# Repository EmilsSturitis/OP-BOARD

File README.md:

# OP-BOARD
Operational amplifier dev board based on the OPA2333

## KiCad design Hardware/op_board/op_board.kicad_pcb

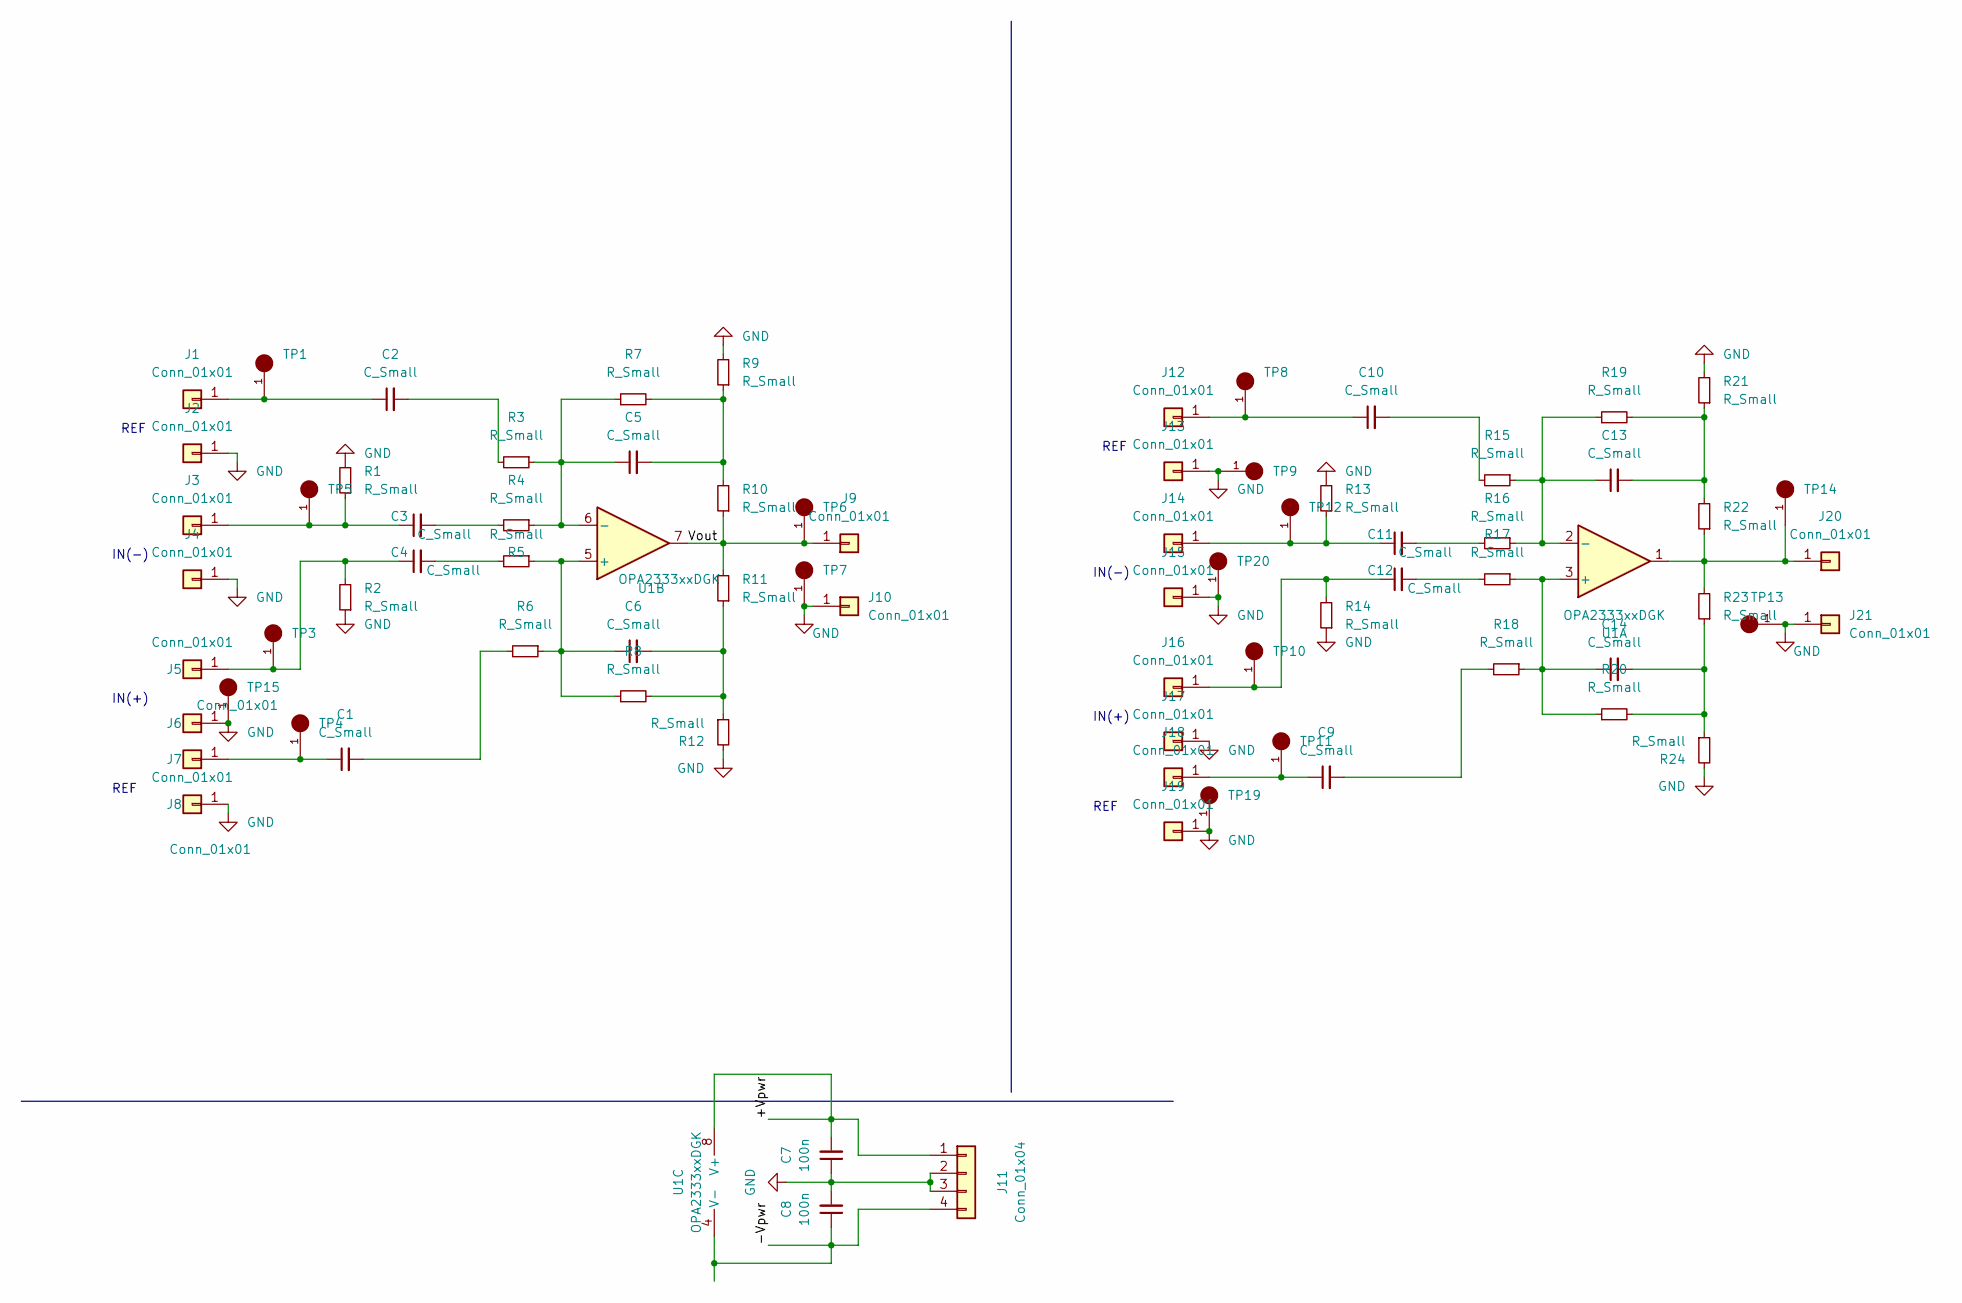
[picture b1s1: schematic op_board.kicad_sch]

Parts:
C1, C2, C3, C4, C5, C6, C9, C10, C11, C12, C13, C14: C_Small; C_0805_2012Metric_Pad1.18x1.45mm_HandSolder
C7, C8: 100n; C_0603_1608Metric
J1, J3, J5, J7, J9, J12, J14, J16, J18, J20: Conn_01x01; TestPoint_THTPad_2.0x2.0mm_Drill1.0mm
J2, J4, J6, J8, J10, J13, J15, J17, J19, J21: Conn_01x01; TestPoint_THTPad_D2.0mm_Drill1.0mm
J11: Conn_01x04; PinHeader_1x04_P2.54mm_Vertical
R1, R2, R3, R4, R5, R6, R7, R8, R9, R10, R11, R12, R13, R14, R15, R16, R17, R18, R19, R20, R21, R22, R23, R24: R_Small; R_0805_2012Metric_Pad1.20x1.40mm_HandSolder
TP1, TP3, TP4, TP5, TP6, TP7, TP8, TP9, TP10, TP11, TP12, TP13, TP14, TP15, TP19, TP20: RCWCTE; TP420X150; PARTREV 1/06/14
U1: OPA2333xxDGK; TSSOP-8_3x3mm_P0.65mm

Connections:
/+Vpwr: C7.2, J11.1, U1.8 (V+)
/-Vpwr: C8.1, J11.4, U1.4 (V-)
/Vout: J9.1, R10.1, R11.2, TP6.1, U1.7
GND: C7.1, C8.2, J2.1, J4.1, J6.1, J8.1, J10.1, J11.2, J11.3, J13.1, J15.1, J17.1, J19.1, J21.1, R1.2, R2.1, R9.2, R12.2, R13.2, R14.1, R21.2, R24.2, TP7.1, TP9.1, TP13.1, TP15.1, TP19.1, TP20.1
unnamed: C1.2, R6.2
unnamed: C2.2, R3.2
unnamed: C3.2, R4.2
unnamed: C4.2, R5.2
unnamed: C5.2, R7.2, R9.1, R10.2
unnamed: C6.2, R8.2, R11.1, R12.1
unnamed: C9.2, R18.2
unnamed: C10.2, R15.2
unnamed: C11.2, R16.2
unnamed: C12.2, R17.2
unnamed: C13.2, R19.2, R21.1, R22.2
unnamed: C14.2, R20.2, R23.1, R24.1
unnamed: C2.1, J1.1, TP1.1
unnamed: C3.1, J3.1, R1.1, TP5.1
unnamed: C4.1, J5.1, R2.2, TP3.1
unnamed: C1.1, J7.1, TP4.1
unnamed: C10.1, J12.1, TP8.1
unnamed: C11.1, J14.1, R13.1, TP12.1
unnamed: C12.1, J16.1, R14.2, TP10.1
unnamed: C9.1, J18.1, TP11.1
unnamed: J20.1, R22.1, R23.2, TP14.1, U1.1
unnamed: C14.1, R17.1, R18.1, R20.1, U1.3 (+)
unnamed: C13.1, R15.1, R16.1, R19.1, U1.2 (-)
unnamed: C6.1, R5.1, R6.1, R8.1, U1.5 (+)
unnamed: C5.1, R3.1, R4.1, R7.1, U1.6 (-)

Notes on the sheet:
IN(-)
IN(+)
REF

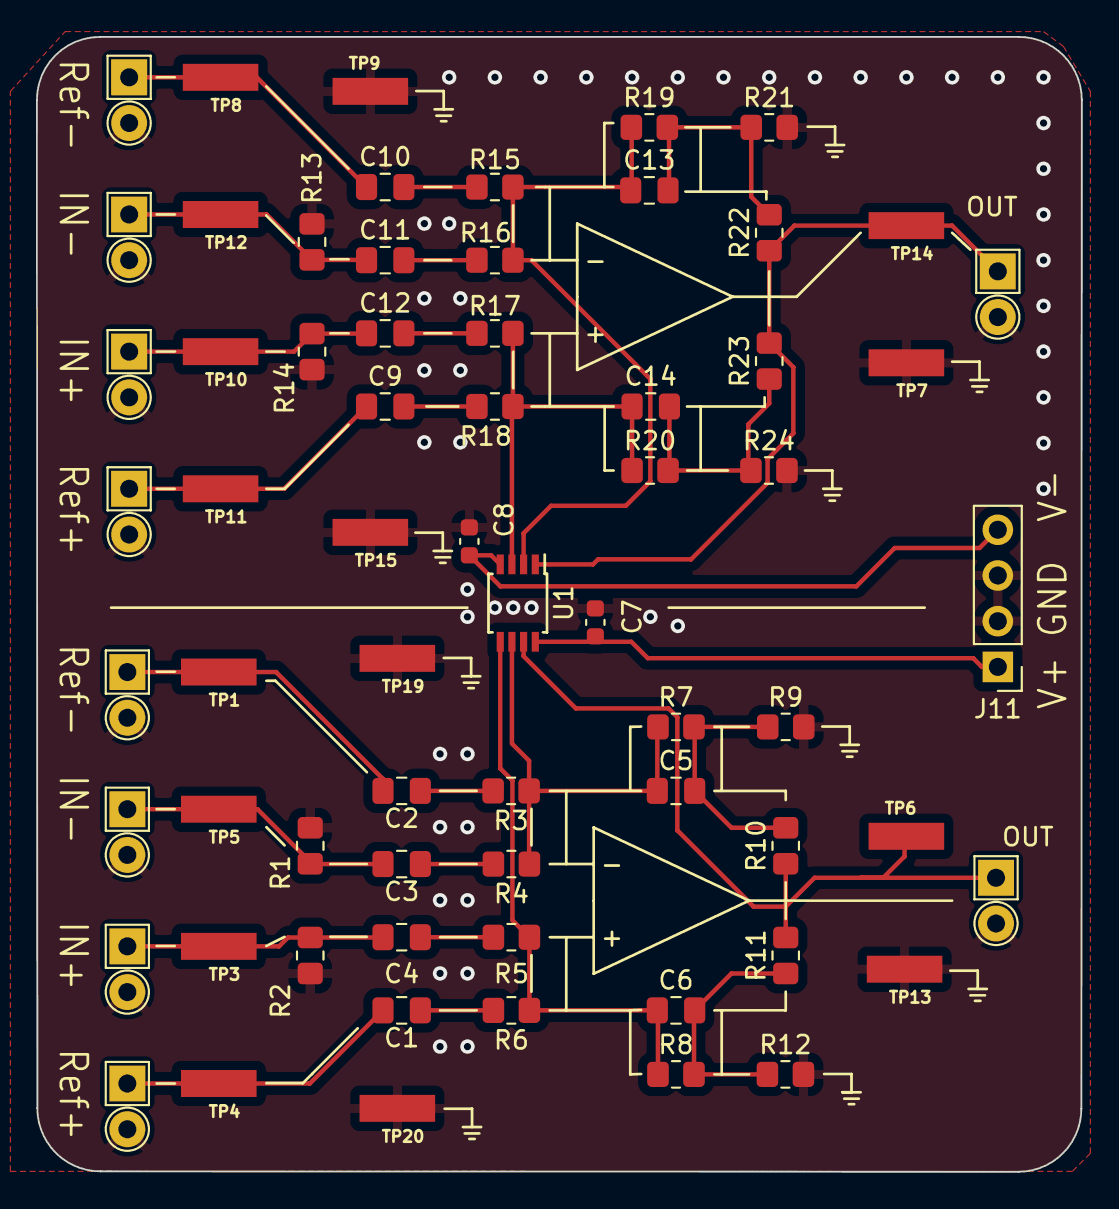
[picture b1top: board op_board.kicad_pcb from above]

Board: 2 copper layers, 58.1 x 63.1 mm, 76 parts (0 on the bottom side), 29 nets.

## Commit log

2023-01-31 small updates
2023-02-02 added filters project
2023-02-28 small updates change to Kicad V7
2023-03-03 small updates, files used for order
2025-07-17 Update to Readme and pictures
2025-07-17 Remove backup ZIPs and update .gitignore
    Deleted multiple backup ZIP files from Hardware/op_board/op_board-backups and added the backup directory to .gitignore to prevent future backups from being tracked in git.
